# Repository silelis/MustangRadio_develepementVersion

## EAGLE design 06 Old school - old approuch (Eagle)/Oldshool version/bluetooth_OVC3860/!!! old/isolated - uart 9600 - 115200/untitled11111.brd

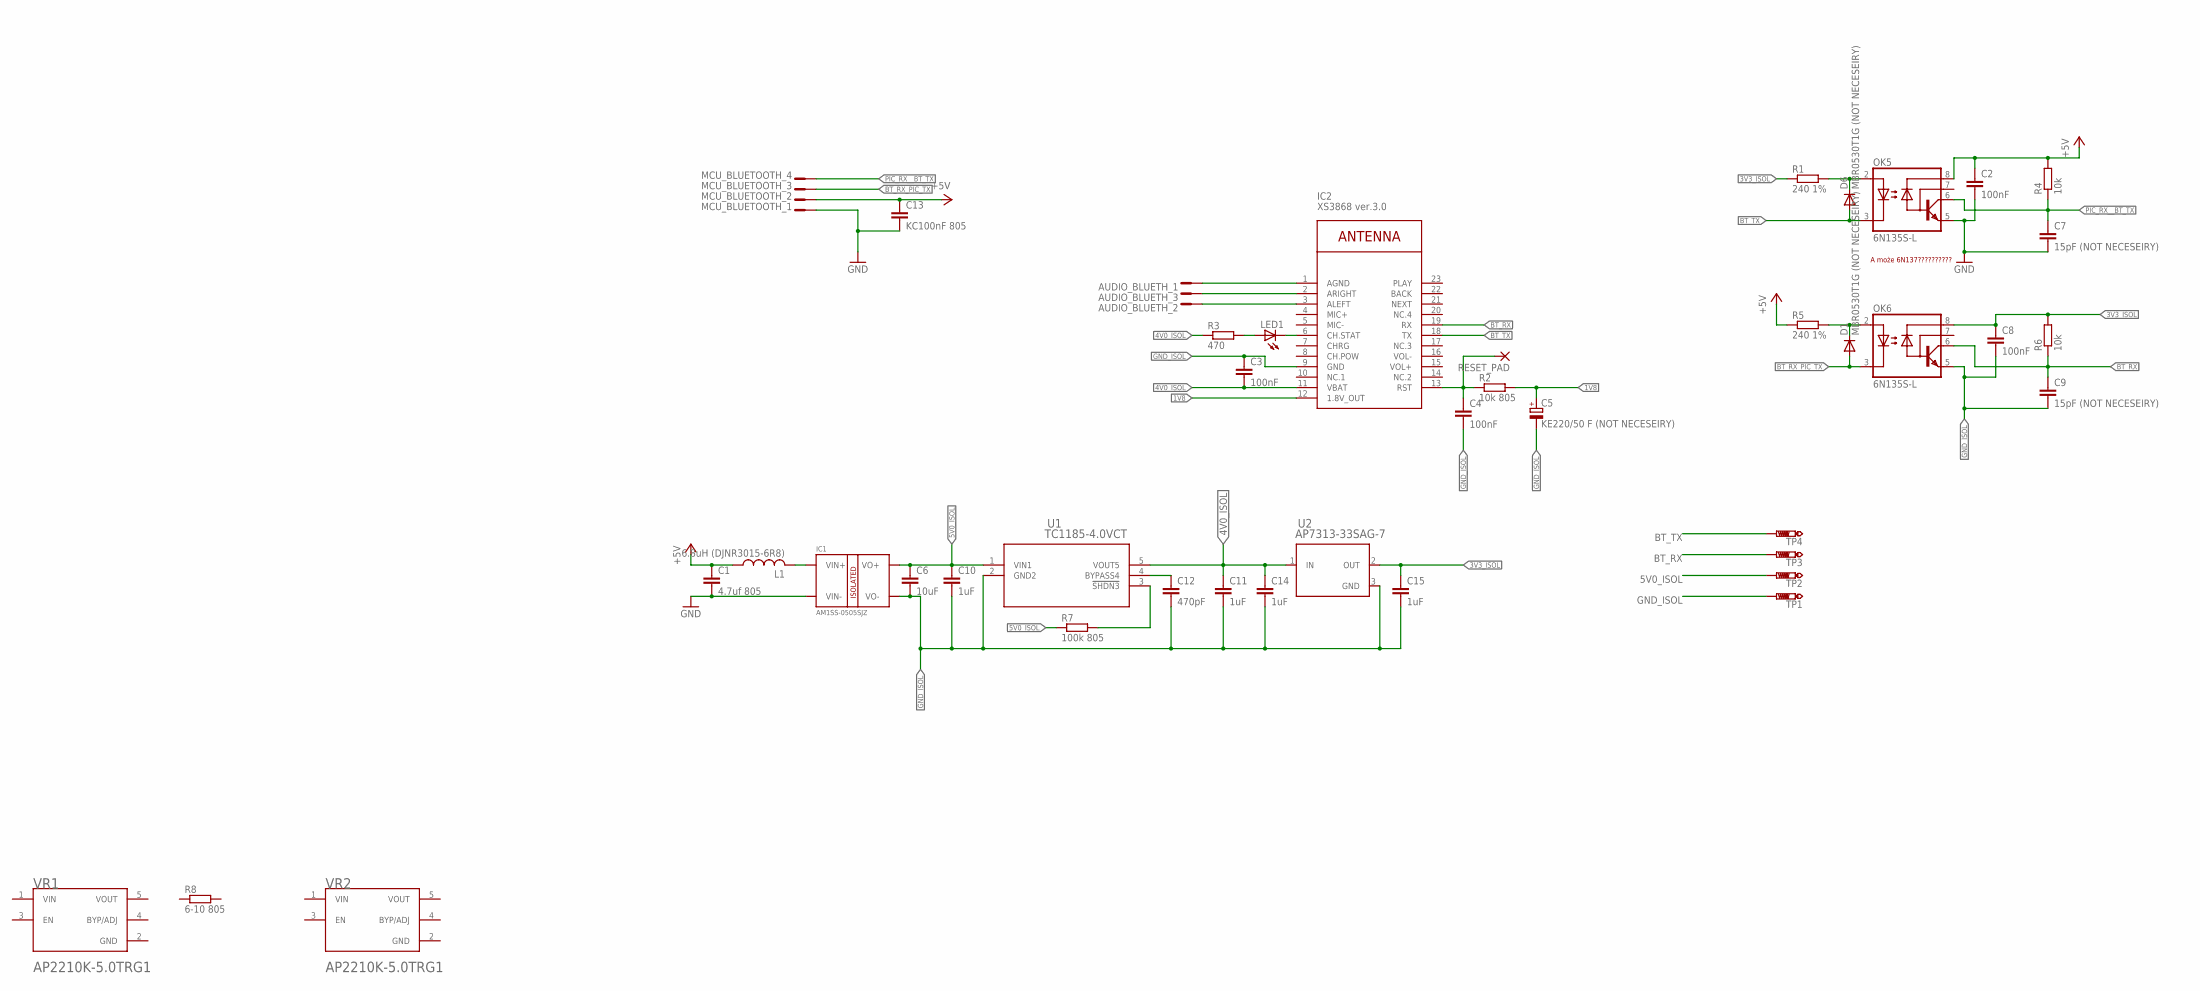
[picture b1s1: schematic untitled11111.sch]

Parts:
AUDIO_BLUETH: JST_3_PIN_B3B-PH-KS; B3B-PH-KS
C1: 4.7uf 805; C0805
C2, C3, C4, C8: 100nF; C0805
C5: KE220/50 F (NOT NECESEIRY); PANASONIC_G
C6: 10uF; C0805
C7, C9: 15pF (NOT NECESEIRY); C0805
C10, C11, C14, C15: 1uF; C0805
C12: 470pF; C0805
C13: KC100nF 805; C0805
D1, D6: MBR0530T1G (NOT NECESEIRY); SOD123
IC1: AM1SS-0505SJZ; SIP4
IC2: XS3868 ver.3.0; WIRELESS-BLUETOOTH-XS3868
L1: 6.8uH (DJNR3015-6R8); L3230M
LED1: LEDSMART-LED; SMART-LED
MCU_BLUETOOTH: JST_4_PIN_B4B-PH-KS; B4B-PH-KS
OK5, OK6: 6N135S-L; DIL8-SMD
R1, R5: 240 1%; M0805
R2: 10k 805; M0805
R3: 470; M0805
R4, R6: 10k; M0805
R7: 100k 805; M0805
R8: 6-10 805; M0805
RESET_PAD: SMD2; SMD1,27-2,54
TP1, TP2, TP3, TP4: PTR1B1,27; B1,27
U1: TC1185-4.0VCT; SOT-23-5_MC-M
U2: AP7313-33SAG-7; SOT-23
VR1, VR2: DIODES_AP2210K-5.0TRG1DIODES_AP2210K-5.0TRG1_0_0; DIODES_AP2210K-5.0TRG1_0

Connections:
1V8: C5.+, IC2.12 (1.8V_OUT), R2.2
3V3_ISOL: C8.1, C15.1, OK6.8 (VCC), R1.1, R6.2, U2.2 (OUT)
4V0_ISOL: C3.2, C11.1, C14.1, IC2.11 (VBAT), R3.1, U1.5 (VOUT5), U2.1 (IN)
5V0_ISOL: C6.1, C10.1, IC1.P$4 (VO+), R7.1, TP2.TP, U1.1 (VIN1)
+5V: C1.1, C2.1, C13.1, L1.1, MCU_BLUETOOTH.P$2, OK5.8 (VCC), R4.2, R5.1
AGND: AUDIO_BLUETH.P$1, IC2.1 (AGND)
BTOUT_LEFT: AUDIO_BLUETH.P$2, IC2.3 (ALEFT)
BTOUT_RIGHT: AUDIO_BLUETH.P$3, IC2.2 (ARIGHT)
BT_LED: IC2.6 (CH.STAT), LED1.B (C)
BT_RX: C9.1, IC2.19 (RX), OK6.6 (VO), R6.1, TP3.TP
BT_RX_PIC_TX: D1.A, MCU_BLUETOOTH.P$3, OK6.3 (C)
BT_TX: D6.A, IC2.18 (TX), OK5.3 (C), TP4.TP
GND: C1.2, C2.2, C7.2, C13.2, IC1.P$1 (VIN-), MCU_BLUETOOTH.P$1, OK5.5 (GND)
GND_ISOL: C3.1, C4.2, C5.-, C6.2, C8.2, C9.2, C10.2, C11.2, C12.2, C14.2, C15.2, IC1.P$3 (VO-), IC2.9 (GND), OK6.5 (GND), TP1.TP, U1.2 (GND2), U2.3 (GND)
unnamed: IC1.P$2 (VIN+), L1.2
unnamed: D6.C, OK5.2 (A), R1.2
unnamed: D1.C, OK6.2 (A), R5.2
unnamed: C12.1, U1.4 (BYPASS4)
unnamed: LED1.A, R3.2
unnamed: R7.2, U1.3 (!SHDN3)
PIC_RX__BT_TX: C7.1, MCU_BLUETOOTH.P$4, OK5.6 (VO), R4.1
RST: C4.1, IC2.13 (RST), R2.1, RESET_PAD.1

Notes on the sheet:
A może 6N137??????????

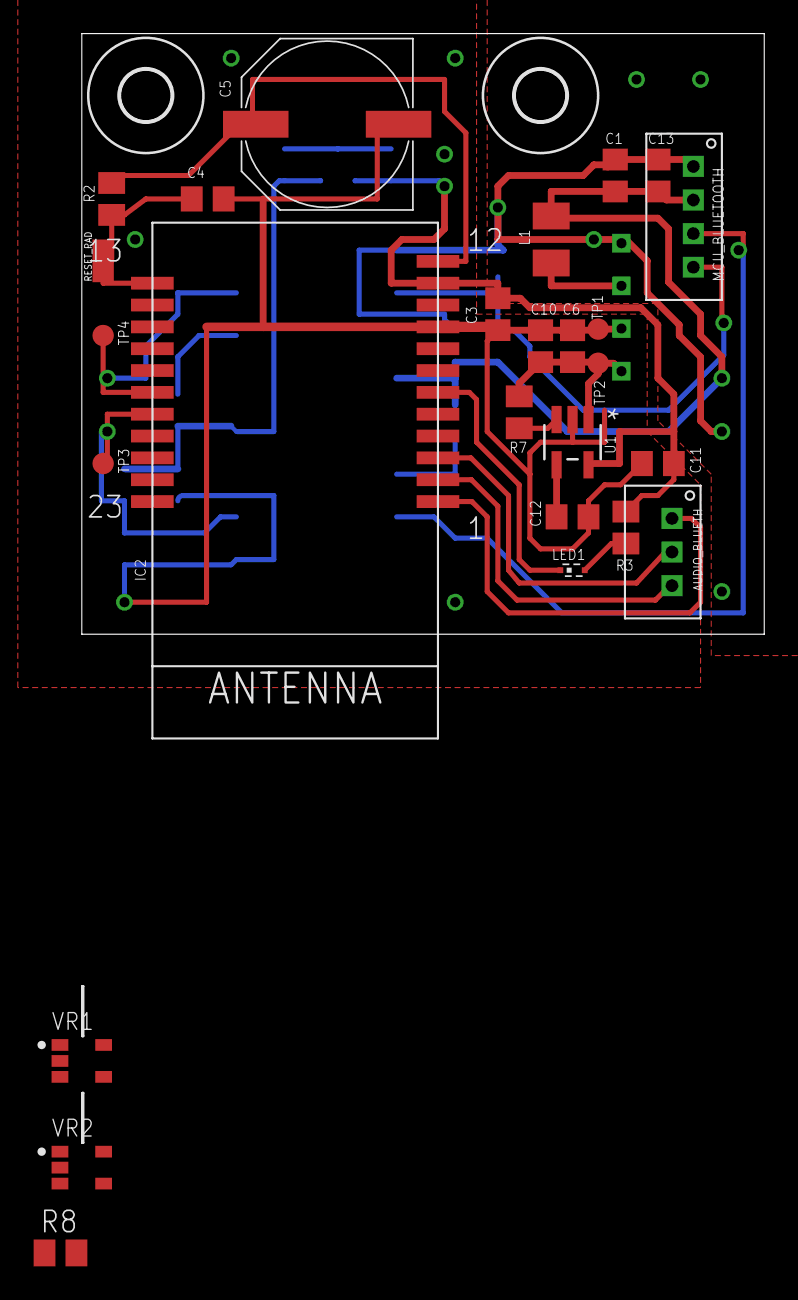
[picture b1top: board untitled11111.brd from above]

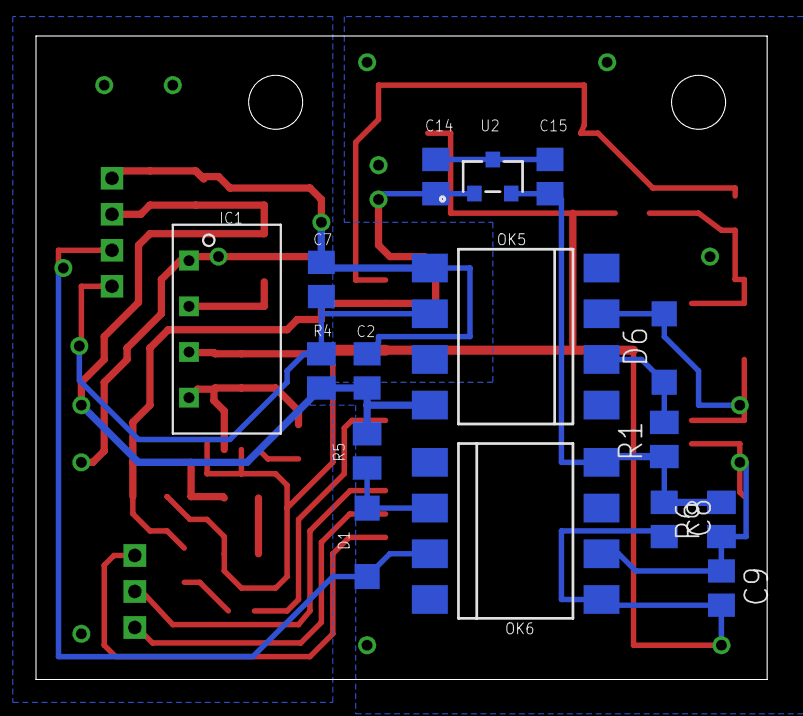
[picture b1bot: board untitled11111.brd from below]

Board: 2 copper layers, 40.6 x 35.8 mm, 44 parts (16 on the bottom side), 22 nets.

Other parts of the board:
U$2, U$3: 3,0

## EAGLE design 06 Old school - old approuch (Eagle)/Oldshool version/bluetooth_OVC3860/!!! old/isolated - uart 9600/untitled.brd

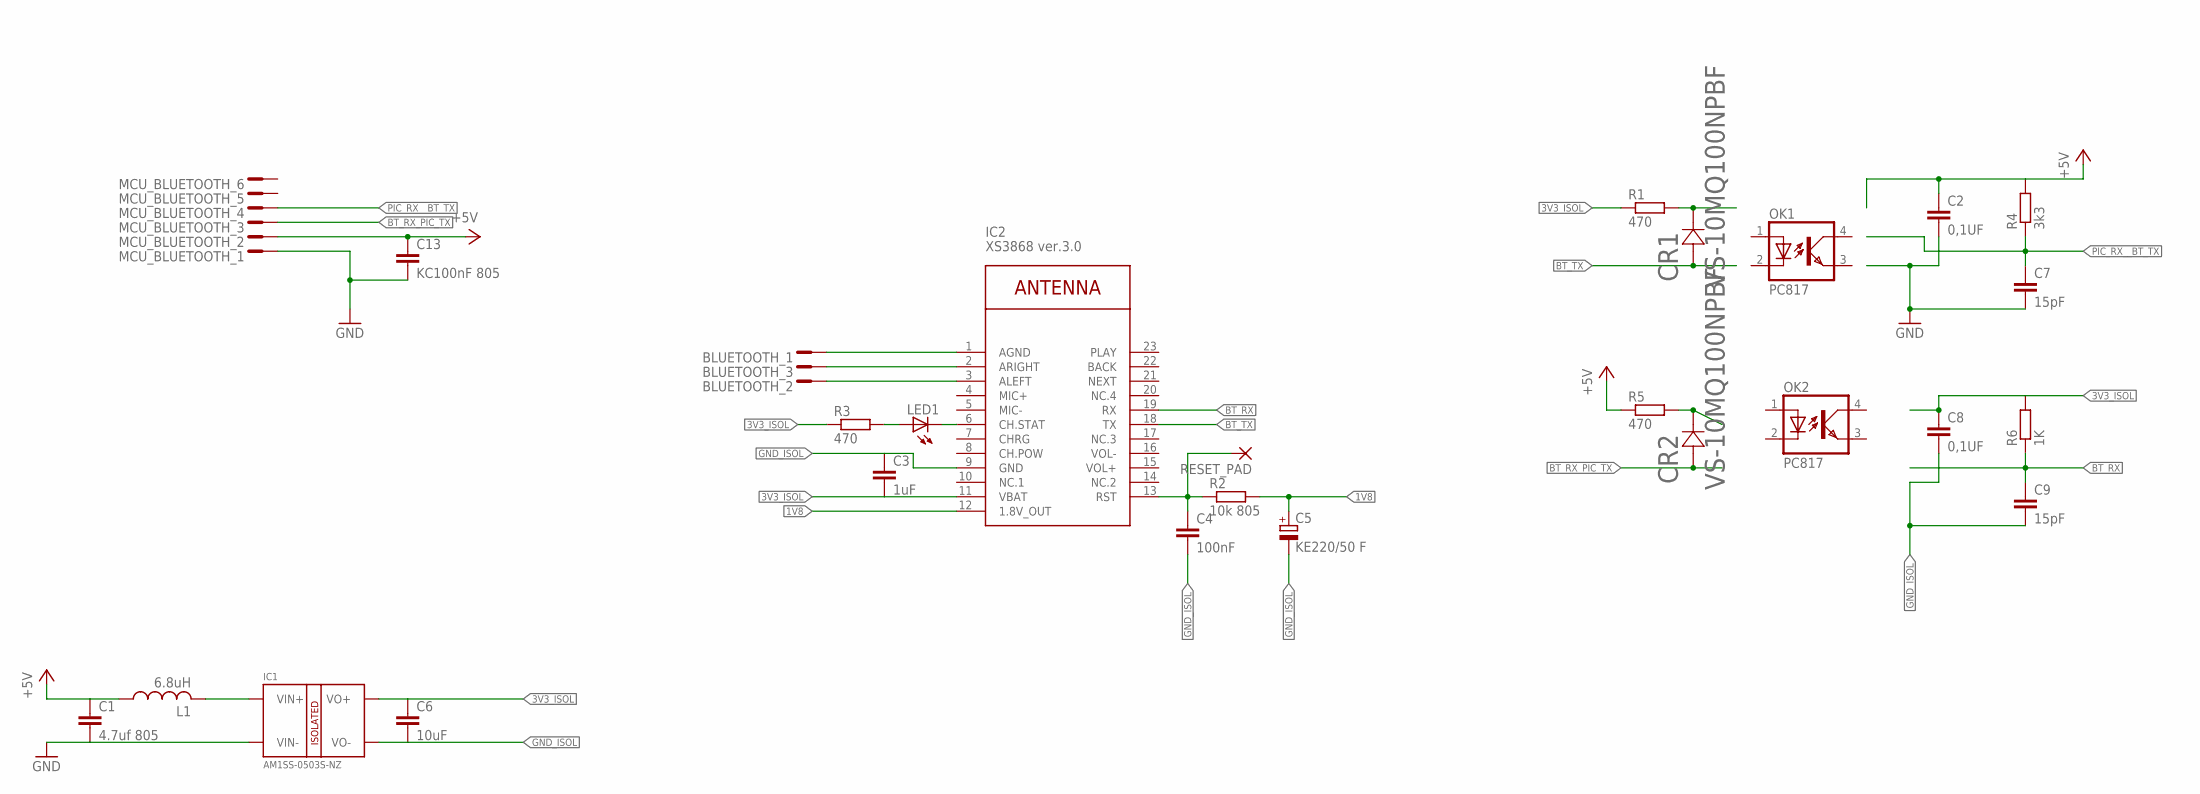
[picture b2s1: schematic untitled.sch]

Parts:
BLUETOOTH: JST_3_PIN_B3B-PH-KS; B3B-PH-KS
C1: 4.7uf 805; C0805
C2, C8: 0,1UF; C0805
C3: 1uF; C0805
C4: 100nF; C0805
C5: KE220/50 F; PANASONIC_G
C6: 10uF; C0805
C7, C9: 15pF; C0805
C13: KC100nF 805; C0805
CR1, CR2: VS-10MQ100NPBF; DIODE_SMA
IC1: AM1SS-0503S-NZ; SIP4
IC2: XS3868 ver.3.0; WIRELESS-BLUETOOTH-XS3868
L1: 6.8uH; 0204/5
LED1: LEDSMART-LED; SMART-LED
MCU_BLUETOOTH: JST_6_PIN_B6B-PH-KS; B6B-PH-KS
OK1, OK2: PC817; DIL04
R1, R3, R5: 470; M0805
R2: 10k 805; M0805
R4: 3k3; M0805
R6: 1K; M0805
RESET_PAD: SMD2; SMD1,27-2,54

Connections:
1V8: C5.+, IC2.12 (1.8V_OUT), R2.2
3V3_ISOL: C3.2, C6.1, C8.1, IC1.P$3 (VO+), IC2.11 (VBAT), R1.1, R3.1, R6.2
+5V: C1.1, C2.1, C13.1, L1.1, MCU_BLUETOOTH.P$2, R4.2, R5.1
AGND: BLUETOOTH.P$1, IC2.1 (AGND)
BTOUT_LEFT: BLUETOOTH.P$2, IC2.3 (ALEFT)
BTOUT_RIGHT: BLUETOOTH.P$3, IC2.2 (ARIGHT)
BT_LED: IC2.6 (CH.STAT), LED1.B (C)
BT_RX: C9.1, IC2.19 (RX), R6.1
BT_RX_PIC_TX: CR2.2 (22), MCU_BLUETOOTH.P$3
BT_TX: CR1.2 (22), IC2.18 (TX)
GND: C1.2, C2.2, C7.2, C13.2, IC1.P$2 (VIN-), MCU_BLUETOOTH.P$1
GND_ISOL: C3.1, C4.2, C5.-, C6.2, C8.2, C9.2, IC1.P$4 (VO-), IC2.9 (GND)
unnamed: IC1.P$1 (VIN+), L1.2
unnamed: CR1.1 (11), R1.2
unnamed: CR2.1 (11), R5.2
unnamed: LED1.A, R3.2
PIC_RX__BT_TX: C7.1, MCU_BLUETOOTH.P$4, R4.1
RST: C4.1, IC2.13 (RST), R2.1, RESET_PAD.1

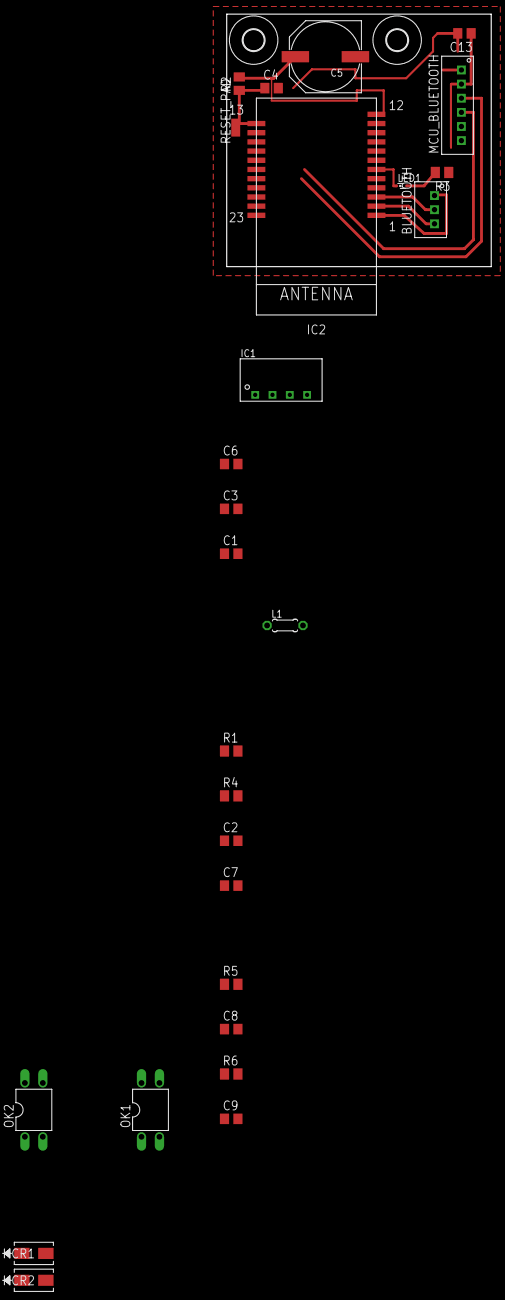
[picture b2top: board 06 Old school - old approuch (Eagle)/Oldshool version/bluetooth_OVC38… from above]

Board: 2 copper layers, 37.4 x 35.8 mm, 29 parts (0 on the bottom side), 18 nets.

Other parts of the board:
U$2, U$3: 3,0

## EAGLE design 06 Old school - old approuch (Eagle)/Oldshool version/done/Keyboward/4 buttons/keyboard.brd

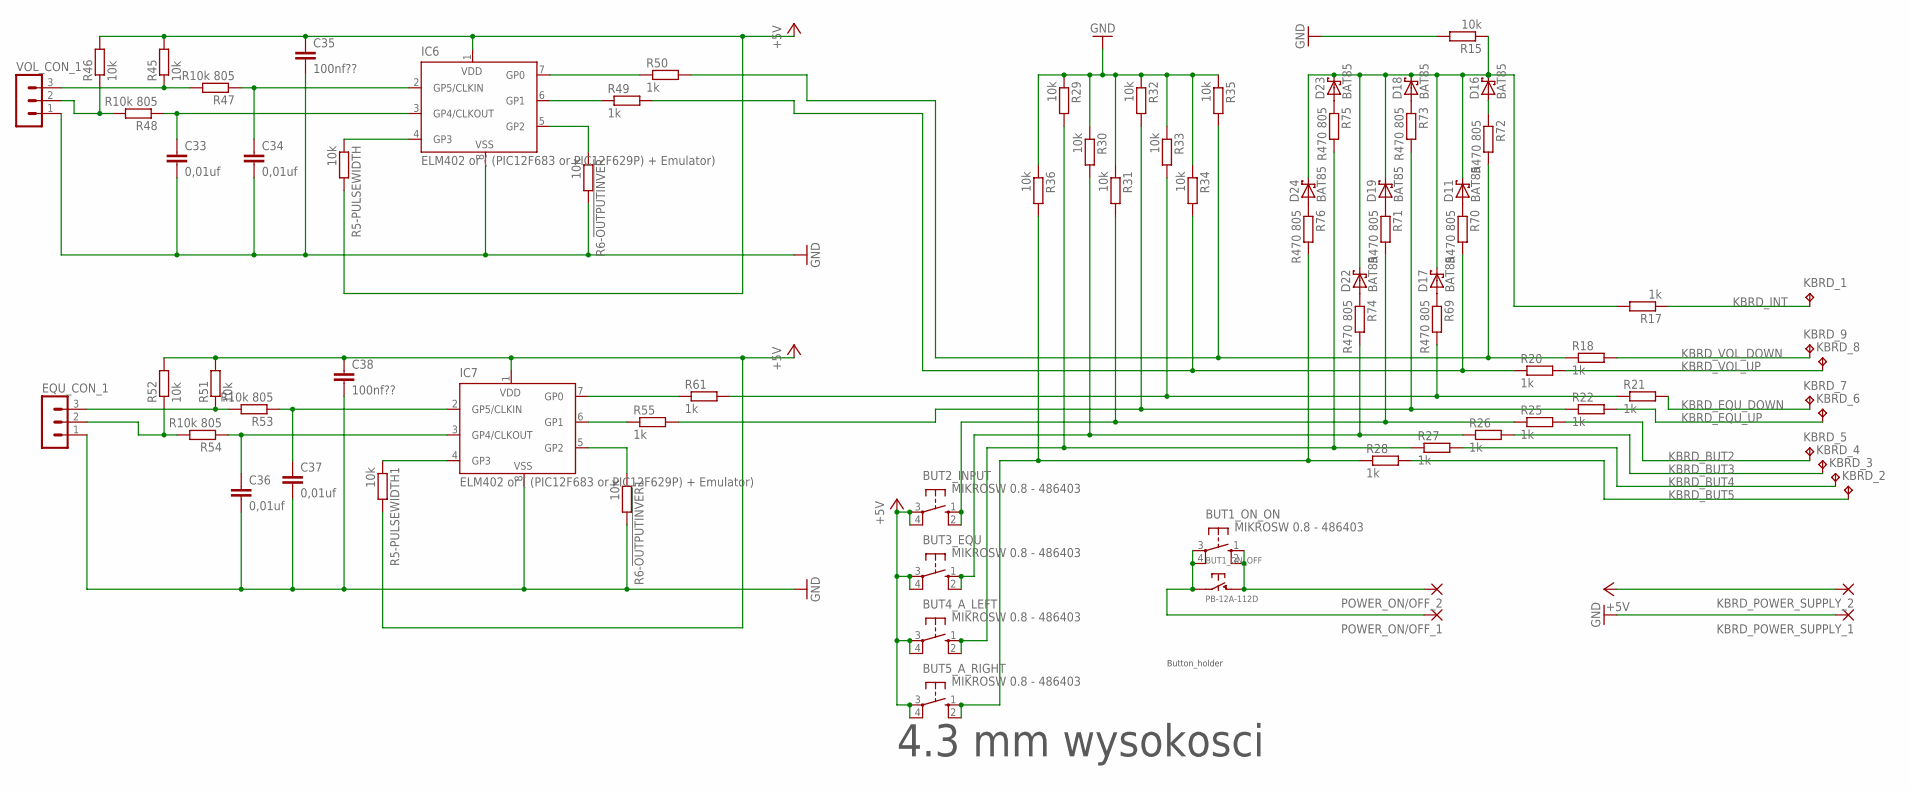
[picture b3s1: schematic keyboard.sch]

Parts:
BUT1_ON_OFF: PB-12A-112D
BUT1_ON_ON, BUT2_INPUT, BUT3_EQU, BUT4_A_LEFT, BUT5_A_RIGHT: MIKROSW 0.8 - 486403; B3F-10XX; MPN B3F-1000
C33, C34, C36, C37: 0,01uf; C0805
C35, C38: 100nf??; C0805
D11, D16, D17, D18, D19, D22, D23, D24: BAT85; DO34-5
EQU_CON_1: MA03-1
IC6, IC7: ELM402 or ( (PIC12F683 or PIC12F629P) + Emulator); DIL8; MPN PIC12F629-E/P
KBRD_1, KBRD_2, KBRD_3, KBRD_4, KBRD_5, KBRD_6, KBRD_7, KBRD_8, KBRD_9: TPPAD1-13Y; P1-13Y
KBRD_POWER_SUPPLY_1, KBRD_POWER_SUPPLY_2: 1,6/0,9
POWER_ON/OFF_1, POWER_ON/OFF_2: 2,15/1,0
R5-PULSEWIDTH, R5-PULSEWIDTH1: 10k; 0204/7
R6-!OUTPUTINVER!, R6-!OUTPUTINVER!1, R15, R29, R30, R36, R45, R46: 10k; R0805
R17, R18, R20, R21, R22, R25, R26, R27, R28, R49, R50, R55, R61: 1k; R0805
R31, R51, R52: 10k; M0805
R32, R33, R34, R35: 10k; 0204/5
R47, R48, R53, R54: R10k 805; R0805
R69, R70, R71, R72, R73, R74, R75, R76: R470 805; R0805
U$1: TRZYMADLO; TRZYMADLO_POPYCHACZY
VOL_CON_1: MA03-1

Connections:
+5V: BUT2_INPUT.3, BUT2_INPUT.4 (P1), BUT3_EQU.3, BUT3_EQU.4 (P1), BUT4_A_LEFT.3, BUT4_A_LEFT.4 (P1), BUT5_A_RIGHT.3, BUT5_A_RIGHT.4 (P1), C35.1, C38.1, IC6.1 (VDD), IC7.1 (VDD), KBRD_POWER_SUPPLY_2.1, R5-PULSEWIDTH.2, R5-PULSEWIDTH1.2, R45.2, R46.2, R51.2, R52.2
GND: C33.2, C34.2, C35.2, C36.2, C37.2, C38.2, EQU_CON_1.1, IC6.8 (VSS), IC7.8 (VSS), KBRD_POWER_SUPPLY_1.1, R6-!OUTPUTINVER!.2, R6-!OUTPUTINVER!1.2, R15.2, R29.1, R30.1, R31.1, R32.1, R33.1, R34.1, R35.1, R36.1, VOL_CON_1.1
KBRD_BUT2: KBRD_5.TP, R25.2
KBRD_BUT3: KBRD_4.TP, R26.2
KBRD_BUT4: KBRD_3.TP, R27.2
KBRD_BUT5: KBRD_2.TP, R28.2
KBRD_EQU_DOWN: KBRD_7.TP, R21.2
KBRD_EQU_UP: KBRD_6.TP, R22.2
KBRD_INT: KBRD_1.TP, R17.1
KBRD_VOL_DOWN: KBRD_9.TP, R18.2
KBRD_VOL_UP: KBRD_8.TP, R20.2
unnamed: R20.1, R34.2, R49.2, R70.2
unnamed: R18.1, R35.2, R50.2, R72.2
unnamed: R22.1, R32.2, R55.2, R73.2
unnamed: R21.1, R33.2, R61.2, R69.2
unnamed: R46.1, R48.2, VOL_CON_1.2
unnamed: R45.1, R47.2, VOL_CON_1.3
unnamed: BUT1_ON_OFF.P$1, BUT1_ON_ON.3, BUT1_ON_ON.4 (P1), POWER_ON/OFF_1.1
unnamed: BUT1_ON_OFF.P$2, BUT1_ON_ON.1 (S), BUT1_ON_ON.2 (S1), POWER_ON/OFF_2.1
unnamed: EQU_CON_1.2, R52.1, R54.2
unnamed: EQU_CON_1.3, R51.1, R53.2
unnamed: BUT2_INPUT.1 (S), BUT2_INPUT.2 (S1), R25.1, R31.2, R71.2
unnamed: BUT3_EQU.1 (S), BUT3_EQU.2 (S1), R26.1, R30.2, R74.2
unnamed: BUT4_A_LEFT.1 (S), BUT4_A_LEFT.2 (S1), R27.1, R29.2, R75.2
unnamed: BUT5_A_RIGHT.1 (S), BUT5_A_RIGHT.2 (S1), R28.1, R36.2, R76.2
unnamed: C34.1, IC6.2 (GP5/CLKIN), R47.1
unnamed: C33.1, IC6.3 (GP4/CLKOUT), R48.1
unnamed: IC6.4 (GP3), R5-PULSEWIDTH.1
unnamed: IC6.5 (GP2), R6-!OUTPUTINVER!.1
unnamed: IC6.6 (GP1), R49.1
unnamed: IC6.7 (GP0), R50.1
unnamed: C37.1, IC7.2 (GP5/CLKIN), R53.1
unnamed: C36.1, IC7.3 (GP4/CLKOUT), R54.1
unnamed: IC7.4 (GP3), R5-PULSEWIDTH1.1
unnamed: IC7.5 (GP2), R6-!OUTPUTINVER!1.1
unnamed: IC7.6 (GP1), R55.1
unnamed: IC7.7 (GP0), R61.1
unnamed: D17.A, R69.1
unnamed: D11.A, R70.1
unnamed: D18.A, R73.1
unnamed: D19.A, R71.1
unnamed: D22.A, R74.1
unnamed: D23.A, R75.1
unnamed: D24.A, R76.1
unnamed: D11.C, D16.C, D17.C, D18.C, D19.C, D22.C, D23.C, D24.C, R15.1, R17.2
unnamed: D16.A, R72.1

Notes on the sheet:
4.3 mm wysokosci

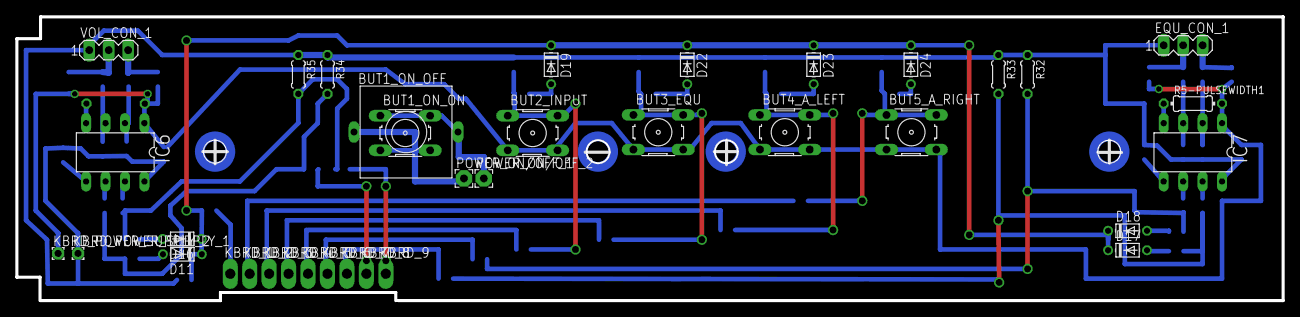
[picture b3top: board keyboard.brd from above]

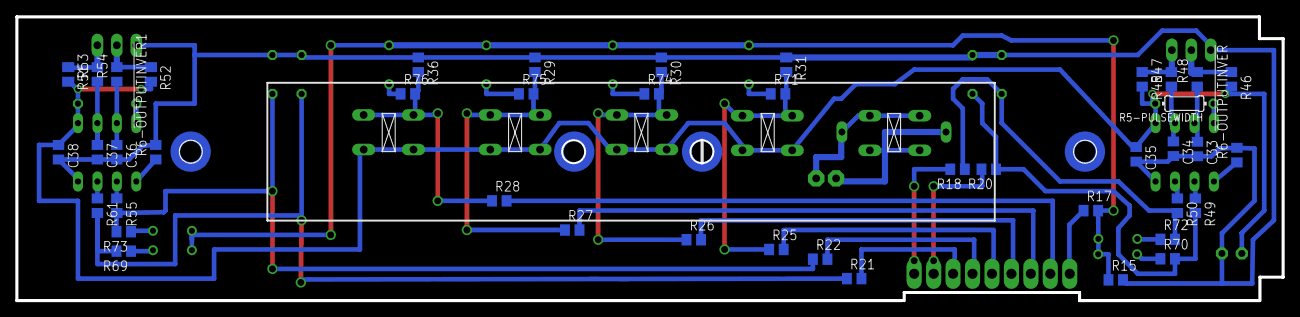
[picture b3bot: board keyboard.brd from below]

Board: 2 copper layers, 165.4 x 37.1 mm, 80 parts (44 on the bottom side), 46 nets.

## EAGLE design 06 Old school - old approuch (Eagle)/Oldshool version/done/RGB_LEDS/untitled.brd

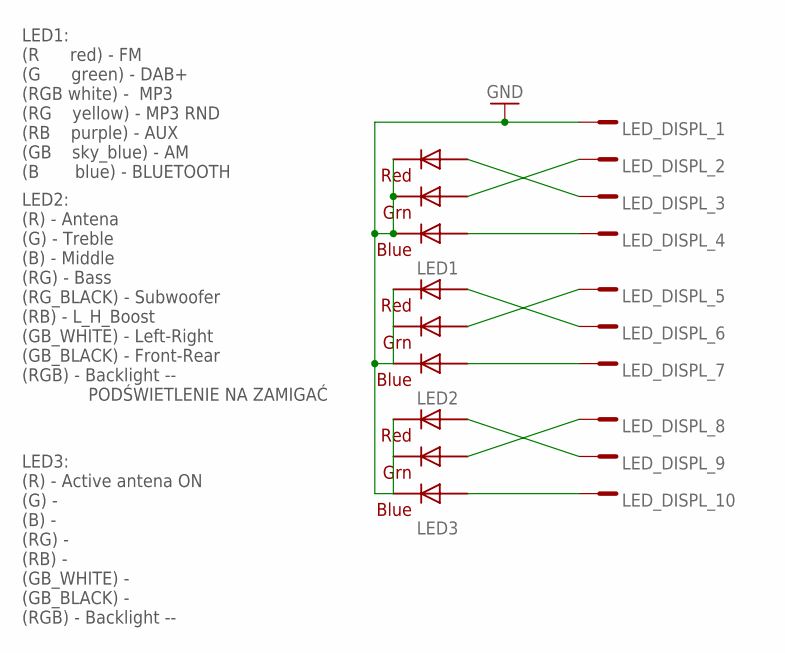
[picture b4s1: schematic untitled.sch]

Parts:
LED1, LED2, LED3: RGBLED5050
LED_DISPL: JST_10_PIN_B10B-PH-SM4-TB; S10B-PH-SM4-TB

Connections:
GND: LED1.4 (BLUE_C), LED1.5 (RED_C), LED1.6 (GREEN_C), LED2.4 (BLUE_C), LED2.5 (RED_C), LED2.6 (GREEN_C), LED3.4 (BLUE_C), LED3.5 (RED_C), LED3.6 (GREEN_C), LED_DISPL.P$1
unnamed: LED2.3 (BLUE_A), LED_DISPL.P$7
unnamed: LED1.3 (BLUE_A), LED_DISPL.P$4
unnamed: LED2.2 (RED_A), LED_DISPL.P$6
unnamed: LED2.1 (GREEN_A), LED_DISPL.P$5
unnamed: LED3.2 (RED_A), LED_DISPL.P$9
unnamed: LED3.1 (GREEN_A), LED_DISPL.P$8
unnamed: LED1.2 (RED_A), LED_DISPL.P$3
unnamed: LED1.1 (GREEN_A), LED_DISPL.P$2
unnamed: LED3.3 (BLUE_A), LED_DISPL.P$10

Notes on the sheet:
LED1: (R red) - FM (G green) - DAB+ (RGB white) - MP3 (RG yellow) - MP3 RND (RB purple) - AUX (GB sky_blue) - AM (B blue) - BLUETOOTH
LED2: (R) - Antena (G) - Treble (B) - Middle (RG) - Bass (RG_BLACK) - Subwoofer (RB) - L_H_Boost (GB_WHITE) - Left-Right (GB_BLACK) - Front-Rear (RGB) - Backlight -- PODŚWIETLENIE NA ZAMIGAĆ
LED3: (R) - Active antena ON (G) - (B) - (RG) - (RB) - (GB_WHITE) - (GB_BLACK) - (RGB) - Backlight --

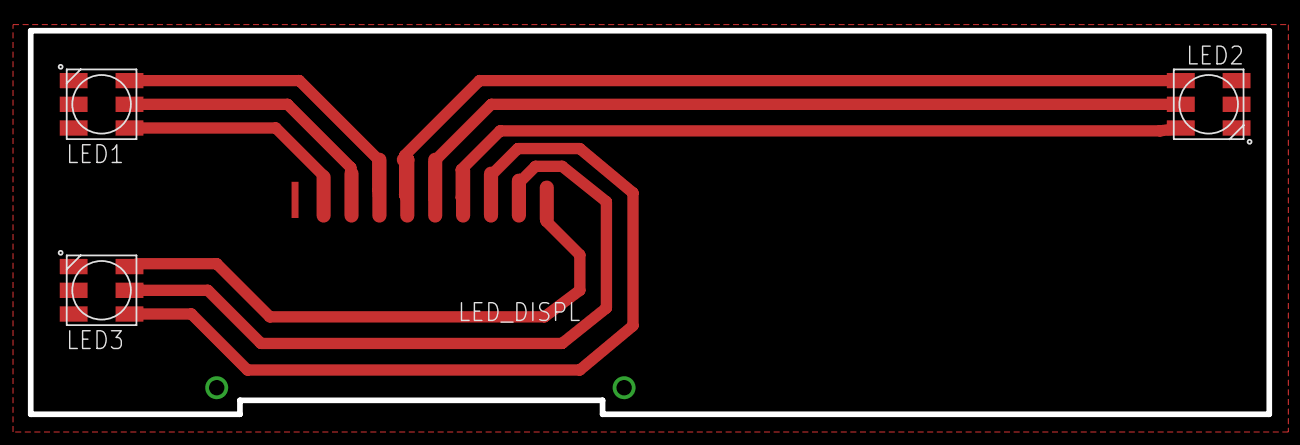
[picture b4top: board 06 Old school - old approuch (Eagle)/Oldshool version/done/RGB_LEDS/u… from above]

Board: 2 copper layers, 88.8 x 27.5 mm, 4 parts (0 on the bottom side), 10 nets.

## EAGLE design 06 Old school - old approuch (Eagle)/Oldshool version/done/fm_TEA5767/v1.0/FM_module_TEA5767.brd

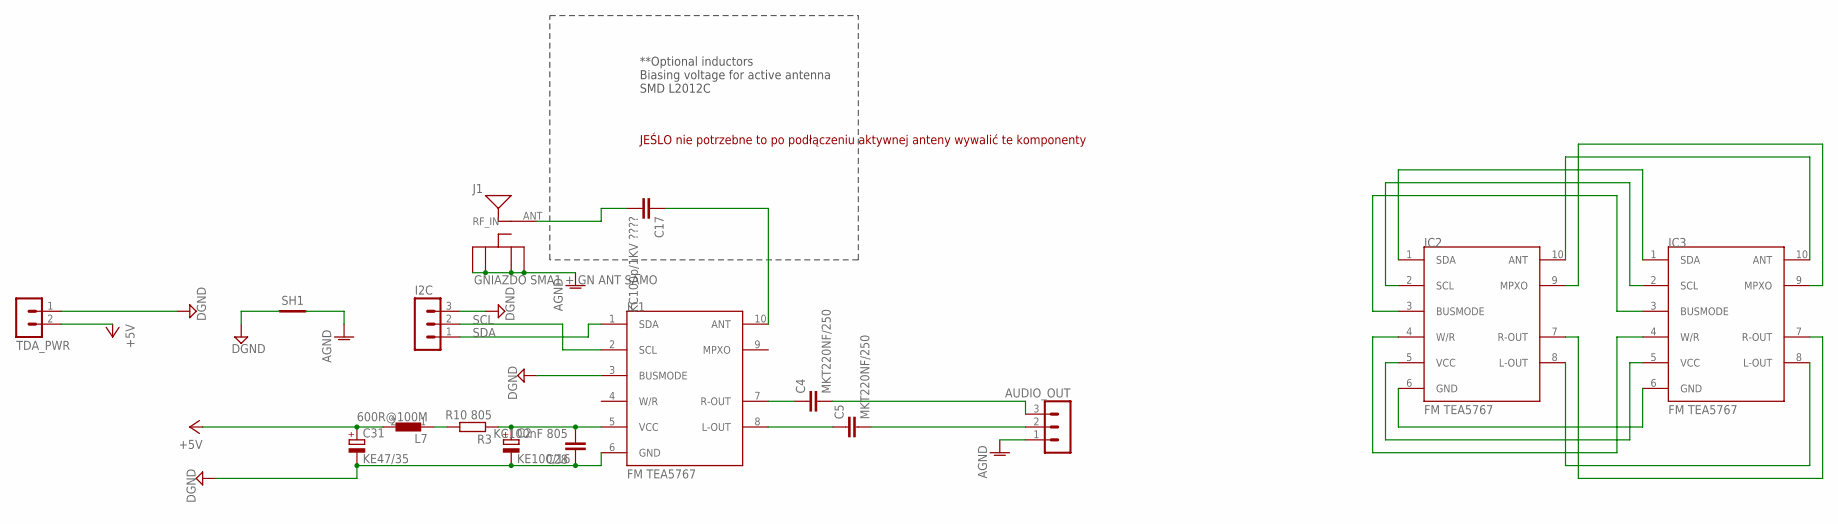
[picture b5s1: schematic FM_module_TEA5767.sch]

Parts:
AUDIO_OUT: MA03-1
C2: KE100/16; TT2D6
C4, C5: MKT220NF/250; C050-050X075
C17: KC100p/1KV ????; C050-025X075
C28: KC100nF 805; C0805
C31: KE47/35; TT2D6
I2C: MA03-1
IC1, IC2: FM TEA5767; PROTOTYPE
IC3: FM TEA5767; SMD
J1: GNIAZDO SMA1 + GN ANT SAMO; 1053378-1
L7: 600R@100M; R0805
R3: R10 805; R0805
SH1: SHORT-HT5; SHORT_TOP-50
TDA_PWR: MA02-1

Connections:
+5V: C31.+, L7.2, TDA_PWR.2
AGND: AUDIO_OUT.1, J1.GND_1 (RFGND_1), J1.GND_2 (RFGND_2), J1.GND_3 (RFGND_3), J1.GND_4 (RFGND_4), SH1.2
DGND: C2.-, C28.1, C31.-, I2C.3, IC1.3 (BUSMODE), IC1.6 (GND), SH1.1, TDA_PWR.1
unnamed: C17.2, J1.ANT (RF_IN)
unnamed: IC2.1 (SDA), IC3.1 (SDA)
unnamed: C2.+, C28.2, IC1.5 (VCC), R3.1
unnamed: C17.1, IC1.10 (ANT)
unnamed: IC2.2 (SCL), IC3.2 (SCL)
unnamed: C4.1, IC1.7 (R-OUT)
unnamed: C5.1, IC1.8 (L-OUT)
unnamed: IC2.3 (BUSMODE), IC3.3 (BUSMODE)
unnamed: IC2.10 (ANT), IC3.10 (ANT)
unnamed: IC2.9 (MPXO), IC3.9 (MPXO)
unnamed: IC2.6 (GND), IC3.6 (GND)
unnamed: IC2.5 (VCC), IC3.5 (VCC)
unnamed: IC2.4 (W/R), IC3.4 (W/R)
unnamed: L7.1, R3.2
unnamed: IC2.8 (L-OUT), IC3.8 (L-OUT)
unnamed: IC2.7 (R-OUT), IC3.7 (R-OUT)
unnamed: AUDIO_OUT.3, C4.2
unnamed: AUDIO_OUT.2, C5.2
SCL: I2C.2, IC1.2 (SCL)
SDA: I2C.1, IC1.1 (SDA)

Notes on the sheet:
**Optional inductors Biasing voltage for active antenna SMD L2012C
JEŚLO nie potrzebne to po podłączeniu aktywnej anteny wywalić te komponenty

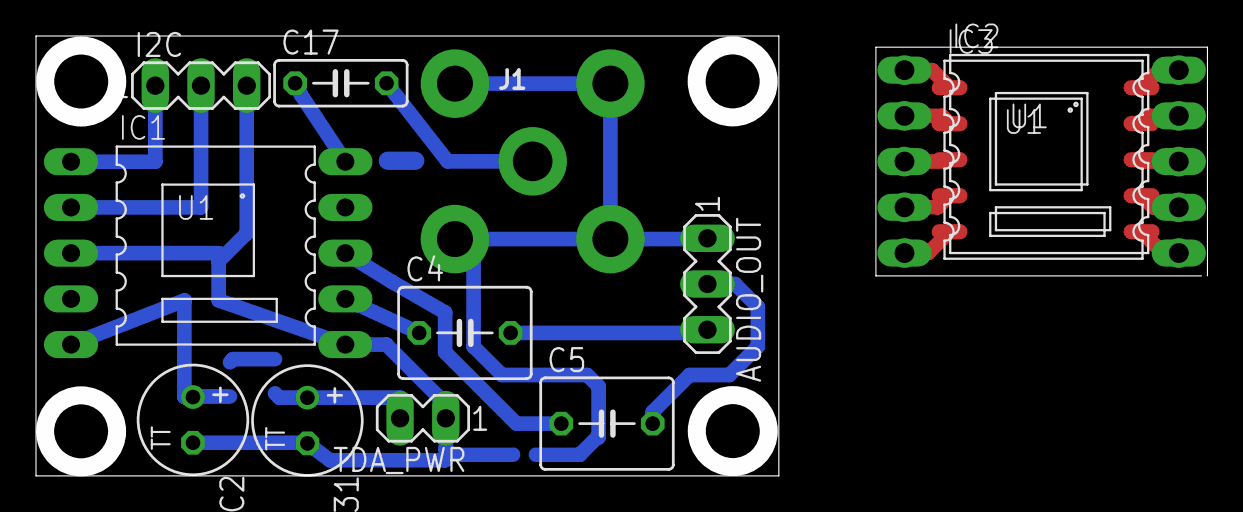
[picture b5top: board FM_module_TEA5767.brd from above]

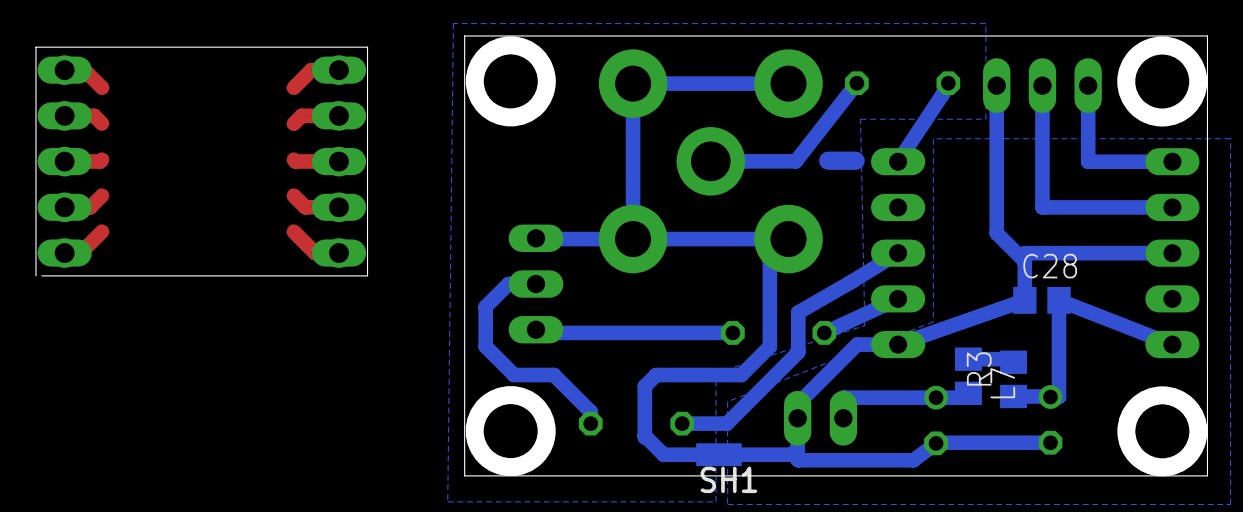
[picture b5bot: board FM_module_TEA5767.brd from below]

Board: 2 copper layers, 41.3 x 24.4 mm, 16 parts (4 on the bottom side), 23 nets.

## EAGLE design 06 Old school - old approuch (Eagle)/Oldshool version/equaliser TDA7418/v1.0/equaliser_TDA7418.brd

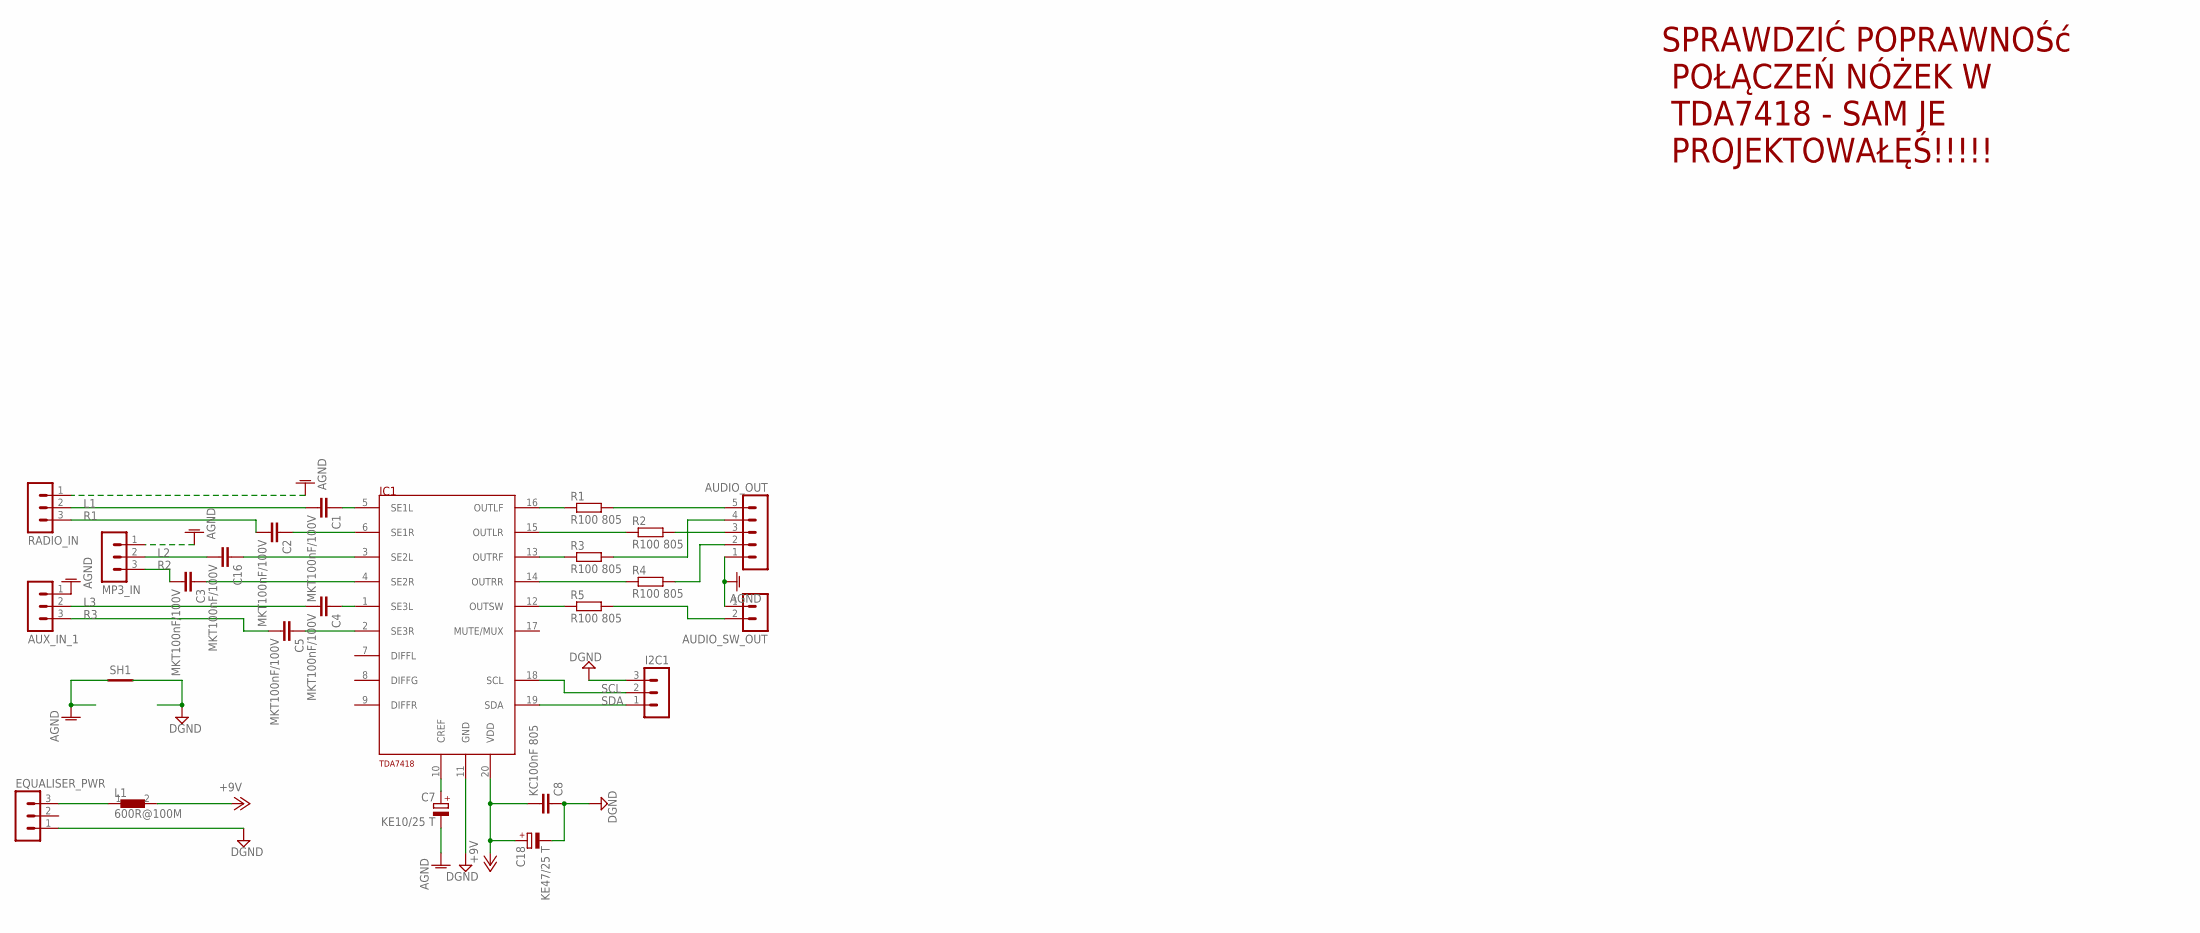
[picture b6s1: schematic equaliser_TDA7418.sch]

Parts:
AUDIO_OUT: MA05-1
AUDIO_SW_OUT: MA02-1
AUX_IN_1: MA03-1
C1, C2, C3, C4, C5, C16: MKT100nF/100V; C050-035X075
C7: KE10/25 T; E1,8-4
C8: KC100nF 805; C0805
C18: KE47/25 T; B45181B
EQUALISER_PWR: MA03-1
I2C1: MA03-1
IC1: TDA7418; SO20
L1: 600R@100M; R0805
MP3_IN: MA03-1
R1, R2, R4, R5: R100 805; 0204V
R3: R100 805; 0204/5
RADIO_IN: MA03-1
SH1: SHORT-HT5; SHORT_TOP-50

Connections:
+12V: C8.2, C18.+, IC1.20 (VDD), L1.2
AGND: AUDIO_OUT.1, AUDIO_SW_OUT.1, AUX_IN_1.1, C7.-, MP3_IN.1, RADIO_IN.1, SH1.1
DGND: C8.1, C18.-, EQUALISER_PWR.1, I2C1.3, IC1.11 (GND), SH1.2
L1: C1.2, RADIO_IN.2
L2: C16.2, MP3_IN.2
L3: AUX_IN_1.2, C4.2
unnamed: EQUALISER_PWR.3, L1.1
unnamed: AUDIO_SW_OUT.2, R5.2
unnamed: C7.+, IC1.10 (CREF)
unnamed: C1.1, IC1.5 (SE1L)
unnamed: C2.1, IC1.6 (SE1R)
unnamed: C16.1, IC1.3 (SE2L)
unnamed: C3.1, IC1.4 (SE2R)
unnamed: C4.1, IC1.1 (SE3L)
unnamed: C5.1, IC1.2 (SE3R)
unnamed: IC1.16 (OUTLF), R1.1
unnamed: IC1.15 (OUTLR), R2.1
unnamed: AUDIO_OUT.4, R3.2
unnamed: AUDIO_OUT.3, R2.2
unnamed: IC1.13 (OUTRF), R3.1
unnamed: AUDIO_OUT.2, R4.2
unnamed: IC1.14 (OUTRR), R4.1
unnamed: IC1.12 (OUTSW), R5.1
unnamed: AUDIO_OUT.5, R1.2
R1: C2.2, RADIO_IN.3
R2: C3.2, MP3_IN.3
R3: AUX_IN_1.3, C5.2
SCL: I2C1.2, IC1.18 (SCL)
SDA: I2C1.1, IC1.19 (SDA)

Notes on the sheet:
SPRAWDZIĆ POPRAWNOŚć POŁĄCZEŃ NÓŻEK W TDA7418 - SAM JE PROJEKTOWAŁĘŚ!!!!!

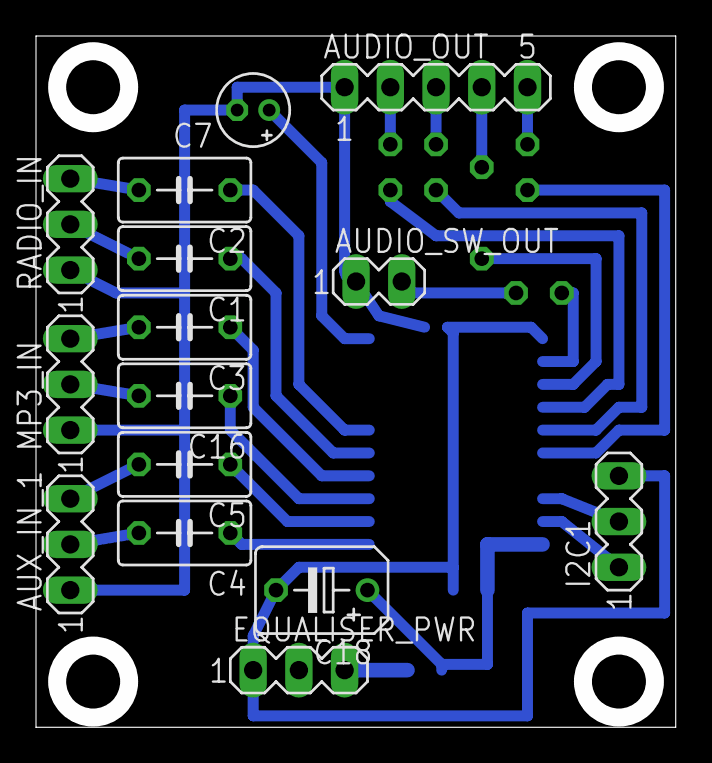
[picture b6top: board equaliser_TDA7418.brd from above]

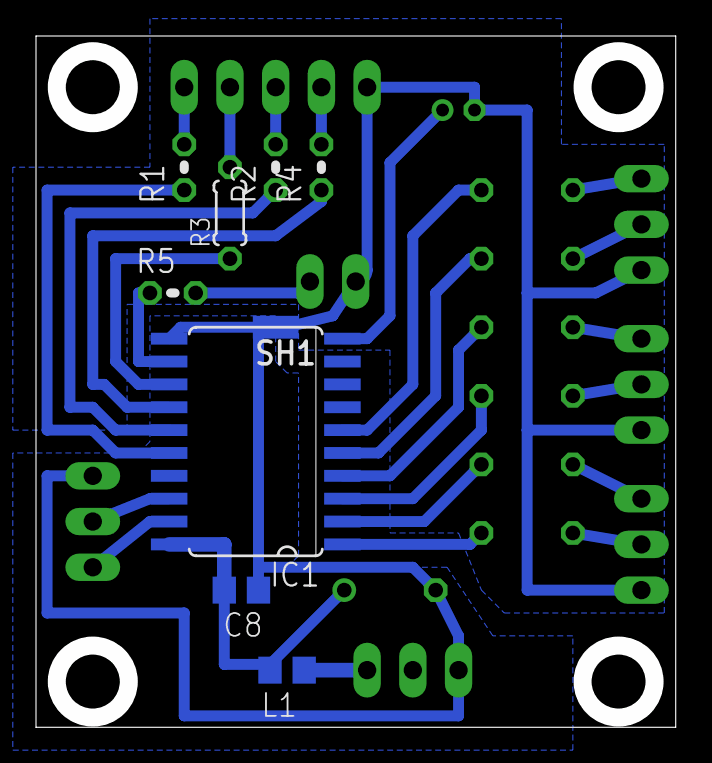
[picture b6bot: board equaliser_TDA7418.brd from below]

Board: 2 copper layers, 35.5 x 38.4 mm, 24 parts (9 on the bottom side), 29 nets.

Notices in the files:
parts and their libraries:
diy-modules: Released under the Creative Commons Attribution 4.0 International License: http://creativecommons.org/licenses/by/4.0
